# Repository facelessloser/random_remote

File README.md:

# random_remote
randomly picks a tv channel for you to watch

Blog post - https://facelesstech.wordpress.com/2016/06/21/random-remote/

Hardware walk through video - https://www.youtube.com/watch?v=GbtydEV3amM

Time lapse hardware build - https://youtu.be/TAFSqzESyxM

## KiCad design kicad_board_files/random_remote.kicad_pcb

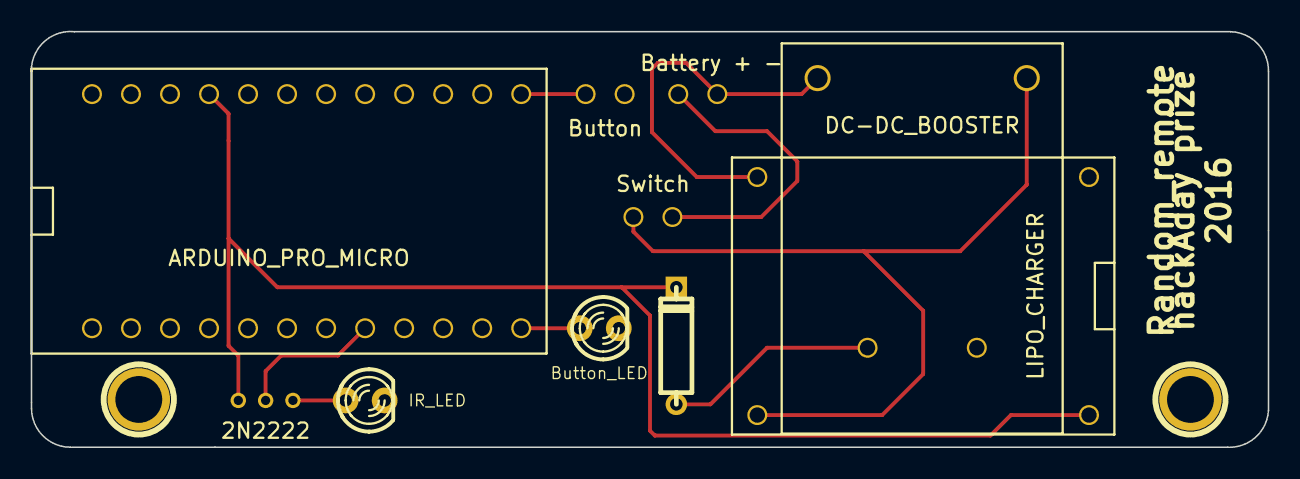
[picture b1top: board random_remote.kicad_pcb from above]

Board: 2 copper layers, 80.5 x 27.1 mm, 13 parts (0 on the bottom side), 10 nets.

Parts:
1PIN, 1PIN#2: P***; 1pin
D1: IR_LED; LED-3MM
D2: Button_LED; LED-3MM
D3: DIODE; D3
Q1: 2N2222
SW1: Switch; 2_pin_misc_custom
SW2: Button; 2_pin_misc_custom
U1: ARDUINO_PRO_MICRO; arduino_leonardo
U2: LIPO_CHARGER; Lipo_charger_custom
U3: DC-DC_BOOSTER; DC-DC_boost
U4: Battery + -; 2_pin_misc_custom
VAL: OSH_final_silks_back

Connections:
unnamed: D3.2, Q1.1, U1.21, U2.3
unnamed: D3.1, U3.4
unnamed: SW1.2, U2.2, U3.2
unnamed: SW1.1, U4.2
unnamed: SW2.1, U1.13
unnamed: U2.1, U3.1, U4.1
unnamed: D1.1, Q1.3
unnamed: D2.1, U1.12
unnamed: Q1.2, U1.8
unnamed: D1.2, D2.2, SW2.2, U1.3, U2.4, U3.3

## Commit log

2016-04-16 Very basic first working code
2016-04-22 Fixed the if statement after the last code change
2016-04-30 Moded files to use library with a arduino leonardo
2016-04-30 Added readme file
2016-04-30 Moved readme file
2016-04-30 Added links
2016-05-16 Gerber files for the board
2016-06-11 renamed folder
2016-06-11 moved code
2016-06-11 Changed name of folder
2016-06-11 Moved and renamed code
2016-06-18 Added new folder with dual button code in it
2016-06-19 added HID code folder
2016-06-20 Cycles through the a list of pre set channels
2016-06-20 Fixed the cycle code
2016-06-21 added links to blog and videos
2016-06-21 Changed some of the channel numbers
2016-09-24 Added board files
